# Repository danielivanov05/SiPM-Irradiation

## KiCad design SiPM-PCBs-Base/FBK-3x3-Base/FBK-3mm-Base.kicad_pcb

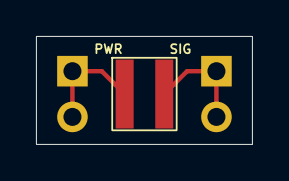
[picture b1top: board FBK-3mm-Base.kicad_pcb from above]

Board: 2 copper layers, 12.0 x 6.0 mm, 3 parts (0 on the bottom side), 2 nets.

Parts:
D1: ASD-RGB3S-P-40
J-SIG-1, J-SIG-2: Conn_01x02_Pin; PinHeader_1x02_P2.54mm_Vertical

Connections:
HV+: D1.1 (K-), J-SIG-2.1, J-SIG-2.2
SIG: D1.2 (A+), J-SIG-1.1, J-SIG-1.2

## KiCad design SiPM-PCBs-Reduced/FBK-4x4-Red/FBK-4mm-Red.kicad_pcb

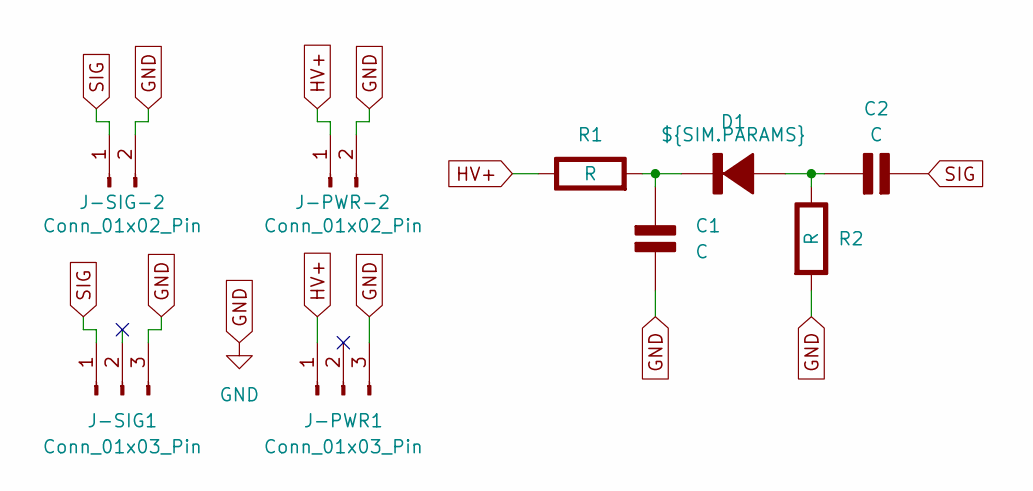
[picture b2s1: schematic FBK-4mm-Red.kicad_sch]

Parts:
C1, C2: C; PinHeader_1x04_P2.54mm_Vertical_Spaced_Mini; Rating V
D1: ${SIM.PARAMS}; ASD-RGB4S-P-40; Rating V/A
J-PWR1: Conn_01x03_Pin; PinHeader_1x03_P2.54mm_Vertical
J-PWR-2: Conn_01x02_Pin; MMCX_Molex_73415-1471_Vertical
J-SIG1: Conn_01x03_Pin; PinHeader_1x03_P2.54mm_Vertical
J-SIG-2: Conn_01x02_Pin; MMCX_Molex_73415-1471_Vertical
R1, R2: R; PinHeader_1x04_P2.54mm_Vertical_Spaced_Mini; Rating W

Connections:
GND: C1.2 (-), J-PWR1.3, J-PWR-2.2, J-SIG1.3, J-SIG-2.2, R2.2 (-)
HV+: J-PWR1.1, J-PWR-2.1, R1.1 (+)
unnamed: C1.1 (+), D1.1 (K-), R1.2 (-)
unnamed: C2.1 (+), D1.2 (A+), R2.1 (+)
SIG: C2.2 (-), J-SIG1.1, J-SIG-2.1

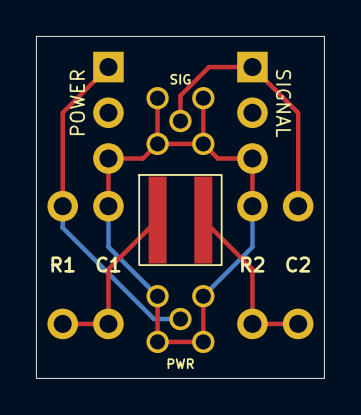
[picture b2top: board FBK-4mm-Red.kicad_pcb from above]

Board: 2 copper layers, 16.0 x 19.0 mm, 9 parts (0 on the bottom side), 5 nets.
